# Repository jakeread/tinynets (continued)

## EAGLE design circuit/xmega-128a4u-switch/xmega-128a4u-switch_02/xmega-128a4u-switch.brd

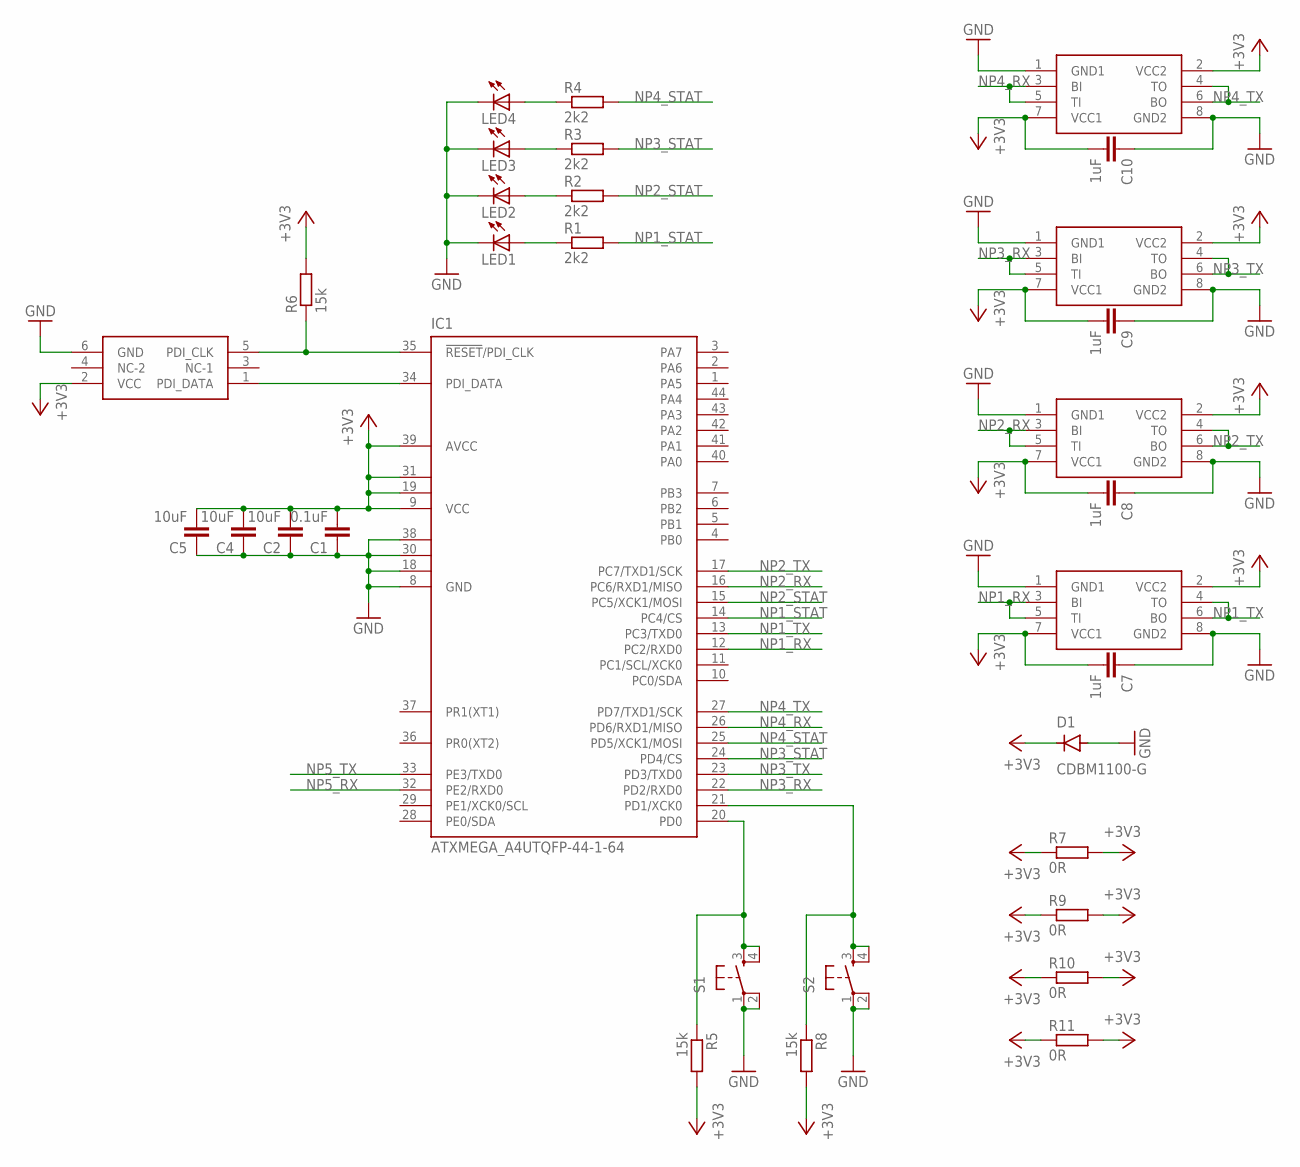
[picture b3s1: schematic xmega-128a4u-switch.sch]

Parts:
C1: 0.1uF; C0805
C2, C4, C5: 10uF; C1206
C7, C8, C9, C10: 1uF; C0805
D1: CDBM1100-G; MINI-SMA
IC1: ATXMEGA_A4UTQFP-44-1-64; TQFP44-13THIN
LED1, LED2, LED3, LED4: LED_E; LED_1206
R1, R2, R3, R4: 2k2; R1206
R5, R6, R8: 15k; R0805
R7, R9, R10, R11: 0R; R1206
S1, S2: 6MM_SWITCH6MM_SWITCH; 6MM_SWITCH
U$3, U$4, U$5, U$6: NETPORT_IDC_FULLFLIP; 2X04SMD
U$7: PDI; 2X03SMD

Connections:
+3V3: C1.2, C2.2, C4.2, C5.2, C7.2, C8.2, C9.2, C10.2, D1.KATHODE, IC1.9 (VCC), IC1.19 (VCC1), IC1.31 (VCC2), IC1.39 (AVCC), R5.2, R6.2, R7.1, R7.2, R8.2, R9.1, R9.2, R10.1, R10.2, R11.1, R11.2, U$3.2 (VCC2), U$3.7 (VCC1), U$4.2 (VCC2), U$4.7 (VCC1), U$5.2 (VCC2), U$5.7 (VCC1), U$6.2 (VCC2), U$6.7 (VCC1), U$7.2 (VCC)
GND: C1.1, C2.1, C4.1, C5.1, C7.1, C8.1, C9.1, C10.1, D1.ANODE, IC1.8 (GND), IC1.18 (GND1), IC1.30 (GND2), IC1.38 (GND3), LED1.C, LED2.C, LED3.C, LED4.C, S1.1, S1.2 (P1), S2.1, S2.2 (P1), U$3.1 (GND1), U$3.8 (GND2), U$4.1 (GND1), U$4.8 (GND2), U$5.1 (GND1), U$5.8 (GND2), U$6.1 (GND1), U$6.8 (GND2), U$7.6 (GND)
unnamed: LED4.A, R4.1
unnamed: LED3.A, R3.1
unnamed: LED2.A, R2.1
unnamed: LED1.A, R1.1
unnamed: IC1.35 (!RESET!/PDI_CLK), R6.1, U$7.5 (PDI_CLK)
unnamed: IC1.34 (PDI_DATA), U$7.1 (PDI_DATA)
unnamed: IC1.20 (PD0), R5.1, S1.3 (S), S1.4 (S1)
unnamed: IC1.21 (PD1/XCK0), R8.1, S2.3 (S), S2.4 (S1)
NP1_RX: IC1.12 (PC2/RXD0), U$3.3 (BI), U$3.5 (TI)
NP1_STAT: IC1.14 (PC4/CS), R1.2
NP1_TX: IC1.13 (PC3/TXD0), U$3.4 (TO), U$3.6 (BO)
NP2_RX: IC1.16 (PC6/RXD1/MISO), U$4.3 (BI), U$4.5 (TI)
NP2_STAT: IC1.15 (PC5/XCK1/MOSI), R2.2
NP2_TX: IC1.17 (PC7/TXD1/SCK), U$4.4 (TO), U$4.6 (BO)
NP3_RX: IC1.22 (PD2/RXD0), U$5.3 (BI), U$5.5 (TI)
NP3_STAT: IC1.24 (PD4/CS), R3.2
NP3_TX: IC1.23 (PD3/TXD0), U$5.4 (TO), U$5.6 (BO)
NP4_RX: IC1.26 (PD6/RXD1/MISO), U$6.3 (BI), U$6.5 (TI)
NP4_STAT: IC1.25 (PD5/XCK1/MOSI), R4.2
NP4_TX: IC1.27 (PD7/TXD1/SCK), U$6.4 (TO), U$6.6 (BO)
NP5_RX: IC1.32 (PE2/RXD0)
NP5_TX: IC1.33 (PE3/TXD0)

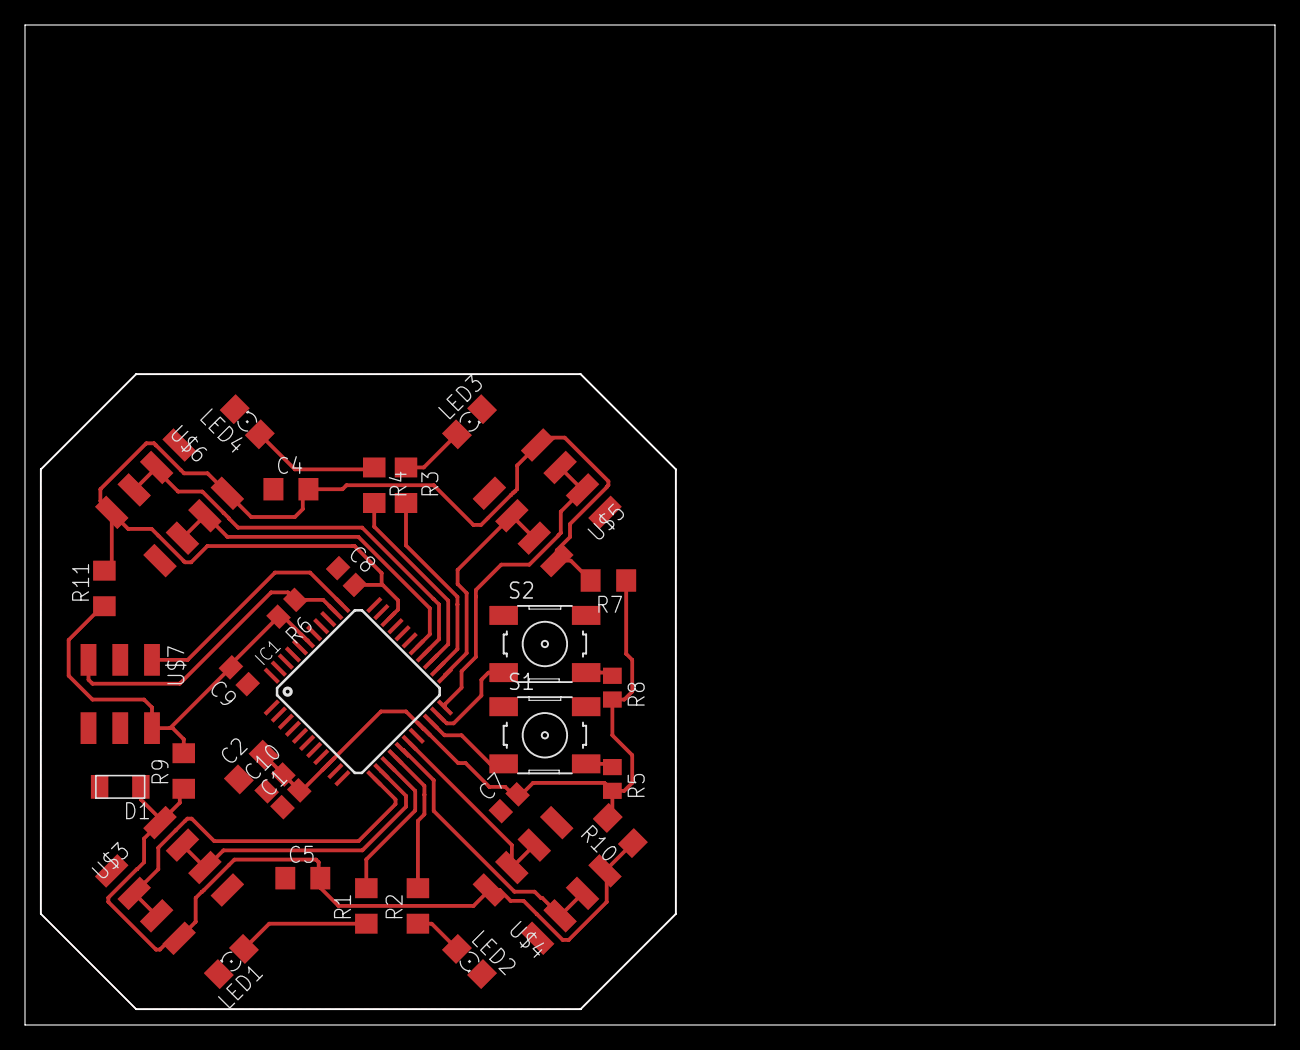
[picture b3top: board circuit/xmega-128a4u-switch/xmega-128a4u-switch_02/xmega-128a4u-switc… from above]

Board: 2 copper layers, 100.0 x 80.0 mm, 32 parts (0 on the bottom side), 22 nets.

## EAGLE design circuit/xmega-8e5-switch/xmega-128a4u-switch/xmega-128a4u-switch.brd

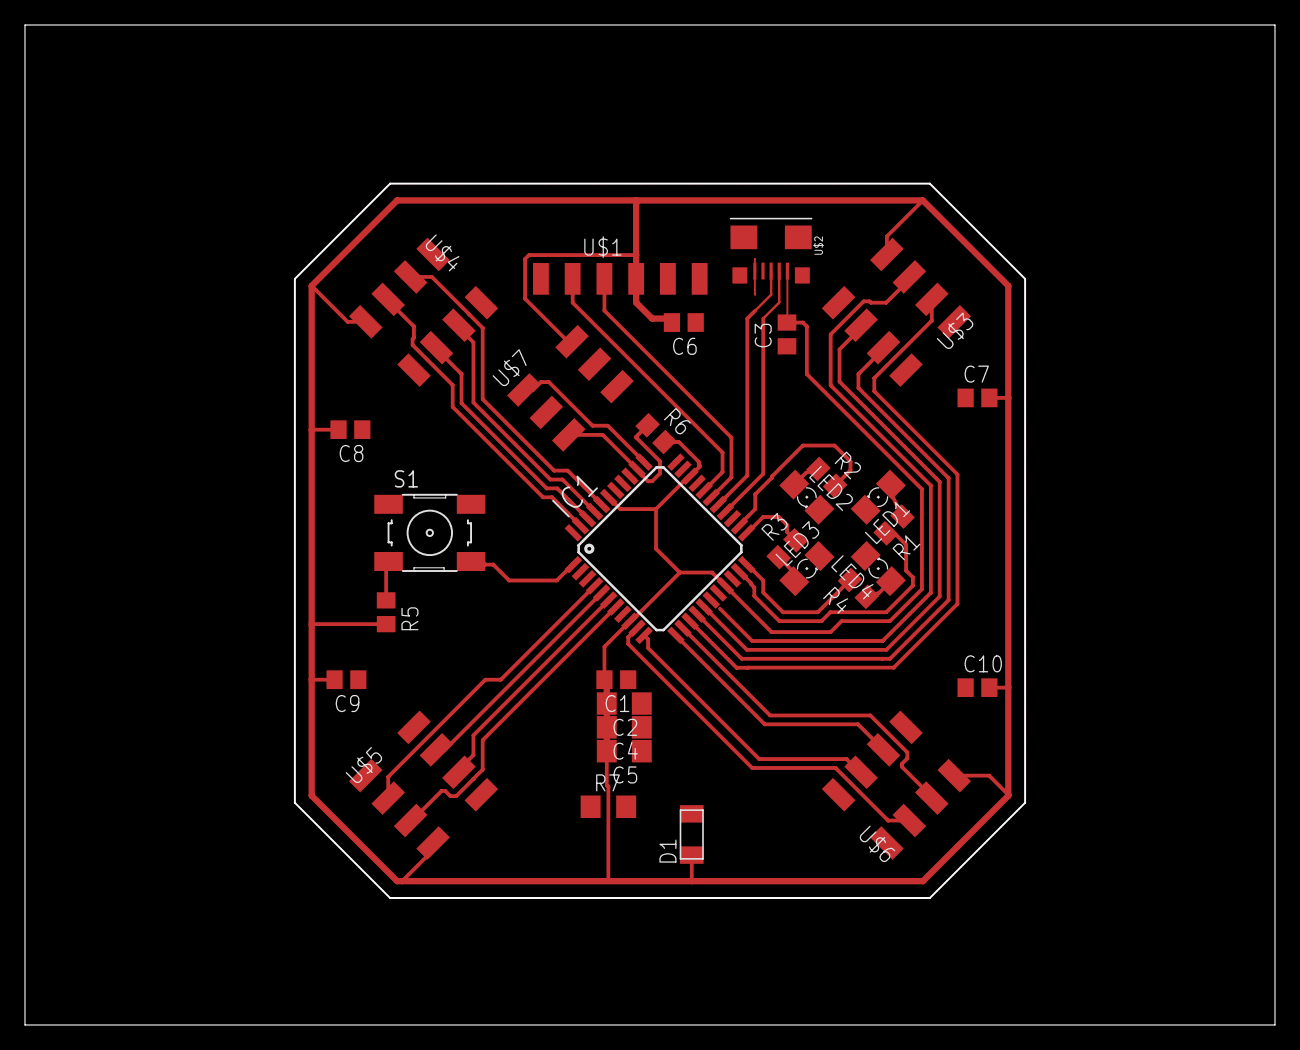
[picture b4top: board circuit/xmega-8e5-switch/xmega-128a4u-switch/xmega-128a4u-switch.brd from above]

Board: 2 copper layers, 100.0 x 80.0 mm, 31 parts (0 on the bottom side), 33 nets.

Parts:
C1: 0.1uF; C0805
C2, C4, C5: 10uF; C1206
C3, C6, C7, C8, C9, C10: 1uF; C0805
D1: CDBM1100-G; MINI-SMA
IC1: XMEGA16A4A; TQFP44
LED1, LED2, LED3, LED4: LED_1206
R1, R2, R3, R4: 2k2; R0805
R5, R6: 15k; R0805
R7: 0R; R1206
S1: 6MM_SWITCH
U$1: FTDI-SMD-HEADER; 1X06SMD
U$2: MICRO-USB_1/64; DX4R005HJ5_64
U$3, U$4, U$5, U$6: NETPORT_IDC_FULLFLIP; 2X04SMD
U$7: PDI; 2X03SMD

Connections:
+3V3: C1.2, C2.2, C3.2, C4.2, C5.2, C6.2, C7.2, C8.2, C9.2, C10.2, D1.KATHODE, IC1.9, IC1.19, IC1.31, IC1.39, R5.2, R6.2, U$1.3, U$2.VBUS, U$3.2, U$3.7, U$4.2, U$4.7, U$5.2, U$5.7, U$6.2, U$6.7, U$7.2
D+: IC1.27, U$2.D+
D-: IC1.26, U$2.D-
GND: C1.1, C2.1, C3.1, C4.1, C5.1, C6.1, C7.1, C8.1, C9.1, C10.1, D1.ANODE, IC1.8, IC1.18, IC1.30, IC1.38, LED1.C, LED2.C, LED3.C, LED4.C, R7.1, R7.2, S1.1, S1.2, U$1.1, U$2.GND, U$3.1, U$3.8, U$4.1, U$4.8, U$5.1, U$5.8, U$6.1, U$6.8, U$7.6
unnamed: LED4.A, R4.1
unnamed: LED3.A, R3.1
unnamed: LED2.A, R2.1
unnamed: LED1.A, R1.1
unnamed: IC1.35, R6.1, U$7.5
unnamed: IC1.34, U$7.1
unnamed: IC1.1, R5.1, S1.3, S1.4
NP1BI: IC1.14, U$3.3
NP1BO: IC1.16, U$3.6
NP1TI: IC1.17, U$3.5
NP1TO: IC1.15, U$3.4
NP1_STAT: IC1.21, R1.2
NP2BI: IC1.40, U$4.3
NP2BO: IC1.42, U$4.6
NP2TI: IC1.43, U$4.5
NP2TO: IC1.41, U$4.4
NP2_STAT: IC1.24, R2.2
NP3BI: IC1.4, U$5.3
NP3BO: IC1.6, U$5.6
NP3TI: IC1.7, U$5.5
NP3TO: IC1.5, U$5.4
NP3_STAT: IC1.23, R3.2
NP4BI: IC1.10, U$6.3
NP4BO: IC1.12, U$6.6
NP4TI: IC1.13, U$6.5
NP4TO: IC1.11, U$6.4
NP4_STAT: IC1.22, R4.2
RX: IC1.28, U$1.4
TX: IC1.29, U$1.5

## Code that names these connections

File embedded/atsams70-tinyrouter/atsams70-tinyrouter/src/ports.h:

/*
 * ports.h
 *
 * Created: 12/8/2017 11:30:49 AM
 *  Author: Jake
 */ 


#ifndef PORTS_H_
#define PORTS_H_


#include "tinyport.h"
#include "ringbuffer.h"
#include "pin.h"

pin_t stlb;
pin_t stlr;
pin_t button;

tinyport_t tp1;
ringbuffer_t p1rbrx;
ringbuffer_t p1rbtx;
pin_t p1lr;
pin_t p1lg;
pin_t p1lb;

tinyport_t tp2;
ringbuffer_t p2rbrx;
ringbuffer_t p2rbtx;
pin_t p2lr;
pin_t p2lg;
pin_t p2lb;

tinyport_t tp3;
ringbuffer_t p3rbrx;
ringbuffer_t p3rbtx;
pin_t p3lr;
pin_t p3lg;
pin_t p3lb;

tinyport_t tp4;
ringbuffer_t p4rbrx;
ringbuffer_t p4rbtx;
pin_t p4lr;
pin_t p4lg;
pin_t p4lb;

tinyport_t* ports[4];

#endif /* PORTS_H_ */

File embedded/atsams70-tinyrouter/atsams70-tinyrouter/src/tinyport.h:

/*
 * tinyport.h
 *
 * Created: 11/23/2017 3:26:50 PM
 *  Author: Jake
 */ 

// port 1
// peripheral c
// uart2
// rx: pd25
// tx: pd26

// port 2
// peripheral a
// uart0
// rx: pa9
// tx: pa10

// port 3
// peripheral c
// uart1
// rx: pa5
// tx: pa4

// port 4
// peripheral c
// uart4
// rx: pd18
// tx: pd19

#ifndef TINYPORT_H_
#define TINYPORT_H_

#define PERIPHERAL_A 0x01
#define PERIPHERAL_B 0x02
#define PERIPHERAL_C 0x03
#define PERIPHERAL_D 0x04

// packet states
#define TP_PACKETSTATE_OUTSIDE 0
#define TP_PACKETSTATE_INSIDE 1

// has packet?
#define TP_NO_PACKET 0
#define TP_HAS_PACKET 1

#define UART_BAUD_DIVIDER 3 // 977: 9600 baud, 81: 115200, 10: 921600, 3: 3.125 MB, 2: 4.687 MB, 1: 9.337 MB
#define RINGBUFFER_SIZE 2048 // in bytes, or 4 full length packets, have 384KBytes total in system

#include "asf.h"
#include "pin.h"
#include "testpins.h"
#include "ringbuffer.h"
#include "packet.h"

typedef struct{
	// hardware
	Uart *uart;
	Pio *port;
	
	uint32_t peripheral_abcd;
	
	uint32_t pinRX_bm;
	uint32_t pinTX_bm;
	
	// status lights
	pin_t *stlr;
	pin_t *stlg;
	pin_t *stlb;
	
	// top-of-pipe buffers 
	ringbuffer_t *rbrx;
	ringbuffer_t *rbtx;
	
	// char handling
	uint8_t haspacket;
	uint8_t packetstate;
	uint8_t packetcounter;
	packet_t packet;
	uint8_t buffersize; // depth of buffer on the other side, updated on heartbeats
	
}tinyport_t;

tinyport_t tinyport_new(Uart *uart, Pio *port, uint32_t peripheral_abcd, uint32_t pinRX_bitmask, uint32_t pinTX_bitmask, ringbuffer_t *rbrx, ringbuffer_t *rbtx, pin_t *stlr, pin_t *stlg, pin_t *stlb);

void tp_init(tinyport_t *tp);

void tp_putchar(tinyport_t *tp, uint8_t data);

int tp_putdata(tinyport_t *tp, uint8_t *data, uint8_t size);

void tp_rxhandler(tinyport_t *tp);

void tp_packetparser(tinyport_t *tp);

void tp_txout(tinyport_t *tp);

void tp_txhandler(tinyport_t *tp);

void tp_testlights(tinyport_t *tp);

#endif /* TINYPORT_H_ */

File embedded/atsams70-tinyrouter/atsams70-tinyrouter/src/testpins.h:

/*
 * testpins.h
 *
 * Created: 12/9/2017 11:34:09 PM
 *  Author: Jake
 */ 


#ifndef TESTPINS_H_
#define TESTPINS_H_

#include "pin.h"

// for testing
pin_t tstrx; // MKHeader P24, PD8
pin_t tsttx; // MKHeader P20, PD4
pin_t tstpckt; // MKHeader P22, PD6
pin_t tstclk; // MKHeader P18, PD2

#endif /* TESTPINS_H_ */

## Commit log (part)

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2017-10-07 add papers, readme
2017-10-11 update with proposal
2017-10-11 image
2017-10-16 update litreview
2017-10-16 readme
2017-10-17 Evaluation lit
2017-10-18 circuit 01
2017-10-19 update proposal, draft 01 report 01, circuit, figures
2017-10-23 async uart
2017-10-25 Add simulation starter code
2017-10-25 two ports
2017-10-25 ports not peers
2017-11-01 add helper functions, readme to sim
2017-11-01 add note about initializing
2017-11-01 markdown format
2017-11-01 Dijkstra
2017-11-02 begin statemachine
2017-11-03 more better
2017-11-03 results from daisy-chain uart message passing
2017-11-03 to readme
2017-11-03 adding raft
2017-11-03 protocol bones
2017-11-03 Create test file for markdown math
2017-11-03 finished markdown algorithm?
2017-11-06 new switch who dis
2017-11-06 update readme w protocol rules
2017-11-06 touchup protocol
2017-11-07 Add buffer and delay to manager
2017-11-07 Packet handling
2017-11-07 touchup
2017-11-07 notes from today's meeting
2017-11-17 new hardware
2017-11-18 new router, readme for pr2
2017-11-18 typos
2017-11-20 How does setInterval work
2017-11-20 Fix issue with buffer checking
2017-11-20 Simulation can send messages to non-neighboring nodes and learn best paths. TODO: incorporate buffer, heartbeat, and disconnect reaction
2017-11-21 Updated Readme with Ethernet worst case chart
2017-11-21 Updated onReceive algorithm
2017-11-21 test and perfomance strategy for other protocols
2017-11-21 forgot to push
2017-11-22 remove cdc
2017-11-22 project report 2
2017-11-22 cleanup circuit directory and documentation
2017-11-23 successful pin abstraction
2017-11-23 complete pin abstraction
2017-11-23 UART Basics
2017-11-23 uart abstracted, all tx lines operating
2017-11-23 final board check is good
2017-11-24 new boards to house
2017-11-29 split circuit and embedded, added BOM
2017-11-30 Heartbeat and disconnect
2017-12-01 Netbeans and sim can run 100 nodes
2017-12-02 Simulates 10000 nodes
2017-12-05 new gitignore, ports all rx-return-interrupting
2017-12-06 packet parsing prototype
2017-12-07 Delays
2017-12-07 port structures
2017-12-07 combined build
2017-12-07 fixed packet_handler
2017-12-08 packet looping
2017-12-08 non-blocking put
2017-12-08 ready to packet handle integrate
2017-12-08 packet handling integrated
2017-12-09 packet handling, acks, bones of application layer
2017-12-10 js does packet assembly from command line
2017-12-10 remove ASF folders
2017-12-10 first successful multi-hop tx/rx
2017-12-10 midpack test complete
2017-12-10 prior to packet refactor
2017-12-11 should be ready for experiments
2017-12-11 update for dougie to debug?
2017-12-12 PDF for realz
2017-12-12 project present
2017-12-12 Node failure recovery
2018-01-24 minor cleanup
2018-08-09 Readme grammar
2018-08-22 Create LICENSE
2018-08-22 Added names to license
2024-03-21 started Automatica submission
2024-03-21 started theory
2024-03-25 figs
2024-03-25 crop schematic
2024-03-25 crop logic analyzer figs
2024-03-25 first draft
2024-03-27 equal authorship
2024-04-05 authors
2024-04-07 Automatica submission
2024-06-19 edits for jnca
2026-05-22 improved makefile
2026-05-22 gitignore elsarticle download
2026-05-22 graphical abstract
2026-05-23 related work
2026-05-23 eval against baseline
2026-05-23 ready for review
2026-05-25 copy editing
2026-05-25 lateflat submission
